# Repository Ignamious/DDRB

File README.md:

# DDRB 
This is a Digital Decade Resistor Box. This is the same as a Decade Resistor box, but uses an Arduino with LCD and Keypad to set the value. This will also allow the user to check the box and insure it's still within spec.

List of Features
  - LCD Readout of Resistance
  - Keypad to set resistance
  - Sub Ohm of .01 - .99 
  - Ohm 2^30 of Resistance ≈ 1,073,741,824 Ohms
  - Modular Cards, Easily replacable for Increased precistion (with Increase of Cst to the board)
  - 2 Expanstion Slots, Each with three Pins to the MCU (Future Expanstion) Signal Does Pass through these.
    - Possible uses
      - reading resistance from start to finish (will require slight rework of Buss Board)
      - Altering Resistance to give "True" value
      - Pulsed Output such as Sig Gen using Resistance values.
  - uses Binary Resistance values to get final resuslts:
    - 1 ohm + 2 ohm + 8 ohm = 11 ohms of resistance ECT. 
      - Should reduce cost

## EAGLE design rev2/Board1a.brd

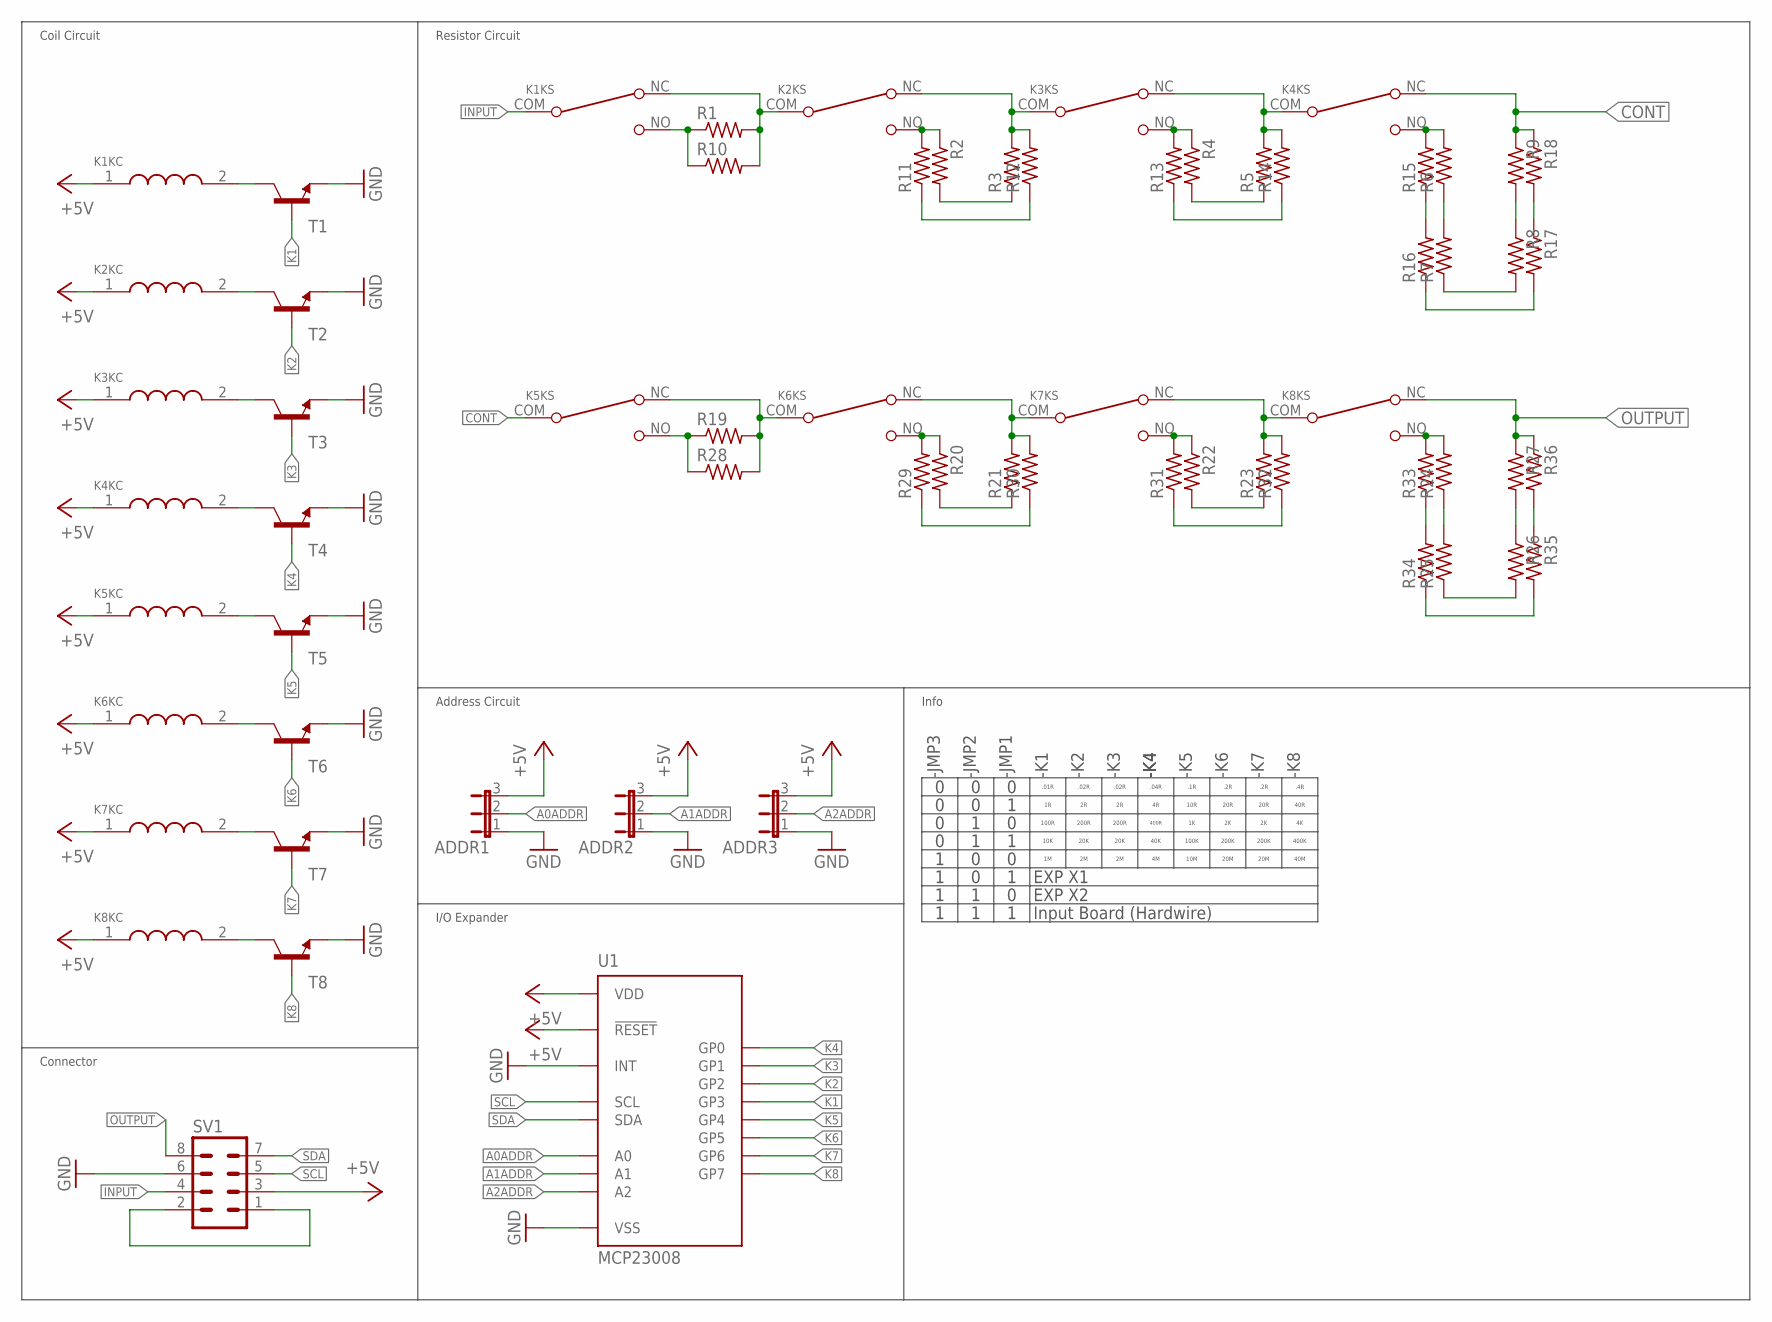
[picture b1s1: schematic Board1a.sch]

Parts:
ADDR1, ADDR2, ADDR3: JP2E; JP2
K1, K5: G5LE-1-VD DC12; G5LE
K2, K3, K4, K6, K7, K8: G5LE
R1, R2, R3, R4, R5, R6, R7, R8, R9, R19, R20, R21, R22, R23, R24, R25, R26, R27: R-US_0613/5V; P0613V
R10, R11, R12, R13, R14, R15, R16, R17, R18, R28, R29, R30, R31, R32, R33, R34, R35, R36: R-US_M1206; M1206
SV1: MA04-2
T1, T2, T3, T4, T5, T6, T7, T8: MMUN2211LT1-NPN-SC59-BEC; SC59-BEC
U1: MCP23008; SOIC

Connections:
+5V: ADDR1.3, ADDR2.3, ADDR3.3, K1.1 (COILA), K2.1 (COILA), K3.1 (COILA), K4.1 (COILA), K5.1 (COILA), K6.1 (COILA), K7.1 (COILA), K8.1 (COILA), SV1.3, U1.P$6 (!RESET), U1.P$18 (VDD)
A0ADDR: ADDR1.2, U1.P$5 (A0)
A1ADDR: ADDR2.2, U1.P$4 (A1)
A2ADDR: ADDR3.2, U1.P$3 (A2)
CONT: K4.NC, K5.COM, R9.1, R18.1
GND: ADDR1.1, ADDR2.1, ADDR3.1, SV1.6, T1.E, T2.E, T3.E, T4.E, T5.E, T6.E, T7.E, T8.E, U1.P$8 (INT), U1.P$9 (VSS)
INPUT: K1.COM, SV1.4
K1: T1.B, U1.P$13 (GP3)
K2: T2.B, U1.P$12 (GP2)
K3: T3.B, U1.P$11 (GP1)
K4: T4.B, U1.P$10 (GP0)
K5: T5.B, U1.P$14 (GP4)
K6: T6.B, U1.P$15 (GP5)
K7: T7.B, U1.P$16 (GP6)
K8: T8.B, U1.P$17 (GP7)
unnamed: K1.NO, R1.1, R10.1
unnamed: K1.NC, K2.COM, R1.2, R10.2
unnamed: R2.2, R3.1
unnamed: K2.NC, K3.COM, R3.2, R12.2
unnamed: SV1.1, SV1.2
unnamed: K2.NO, R2.1, R11.2
unnamed: K3.NC, K4.COM, R5.2, R14.2
unnamed: K3.NO, R4.1, R13.2
unnamed: K4.NO, R6.2, R15.2
unnamed: R4.2, R5.1
unnamed: K3.2 (COILB), T3.C
unnamed: R6.1, R7.2
unnamed: K1.2 (COILB), T1.C
unnamed: R7.1, R8.2
unnamed: K2.2 (COILB), T2.C
unnamed: R8.1, R9.2
unnamed: K4.2 (COILB), T4.C
unnamed: R15.1, R16.2
unnamed: R16.1, R17.2
unnamed: R17.1, R18.2
unnamed: R11.1, R12.1
unnamed: R13.1, R14.1
unnamed: K5.NC, K6.COM, R19.2, R28.2
unnamed: K6.NC, K7.COM, R21.2, R30.2
unnamed: K7.NC, K8.COM, R23.2, R32.2
unnamed: K5.NO, R19.1, R28.1
unnamed: R20.2, R21.1
unnamed: K6.NO, R20.1, R29.2
unnamed: K7.NO, R22.1, R31.2
unnamed: R22.2, R23.1
unnamed: K8.NO, R24.2, R33.2
unnamed: R24.1, R25.2
unnamed: R25.1, R26.2
unnamed: R26.1, R27.2
unnamed: R33.1, R34.2
unnamed: R34.1, R35.2
unnamed: R35.1, R36.2
unnamed: R29.1, R30.1
unnamed: R31.1, R32.1
unnamed: K7.2 (COILB), T7.C
unnamed: K5.2 (COILB), T5.C
unnamed: K6.2 (COILB), T6.C
unnamed: K8.2 (COILB), T8.C
OUTPUT: K8.NC, R27.1, R36.1, SV1.8
SCL: SV1.5, U1.P$1 (SCL)
SDA: SV1.7, U1.P$2 (SDA)

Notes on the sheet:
-JMP3
-JMP2
-JMP1
-K1
-K2
-K3
-K4
.01R
.1R
.02R
.04R
.2R
.4R
10R
100R
20R
200R
40R
400R
10K
100K
20K
200K
40K
400K
-K5
-K6
-K7
-K8
Coil Circuit
Connector
Resistor Circuit
Address Circuit
I/O Expander
Info
10M
20M
40M
EXP X1
EXP X2

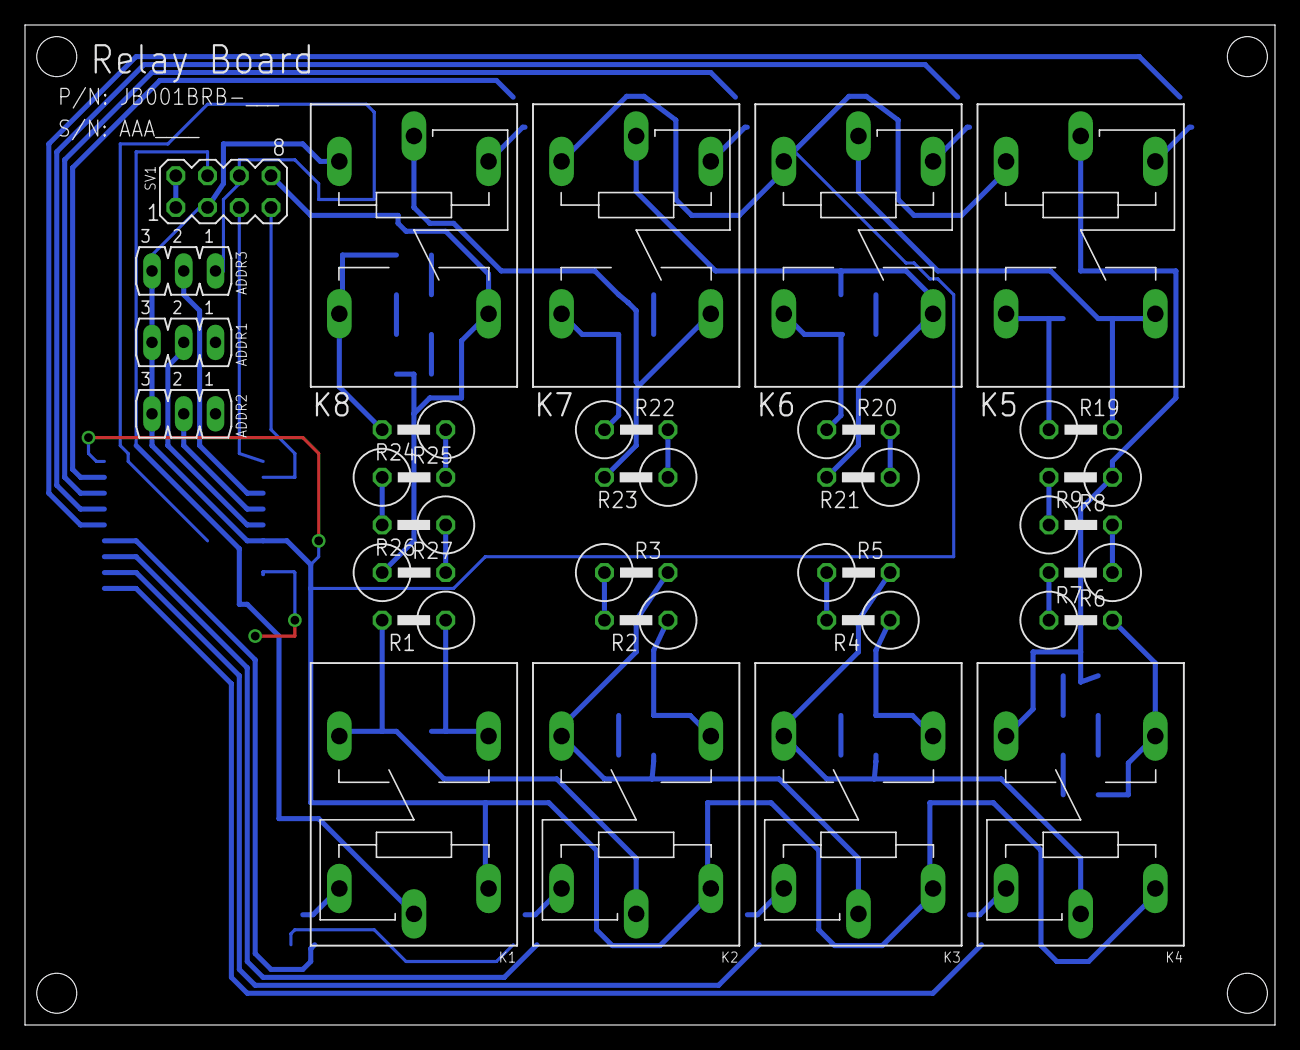
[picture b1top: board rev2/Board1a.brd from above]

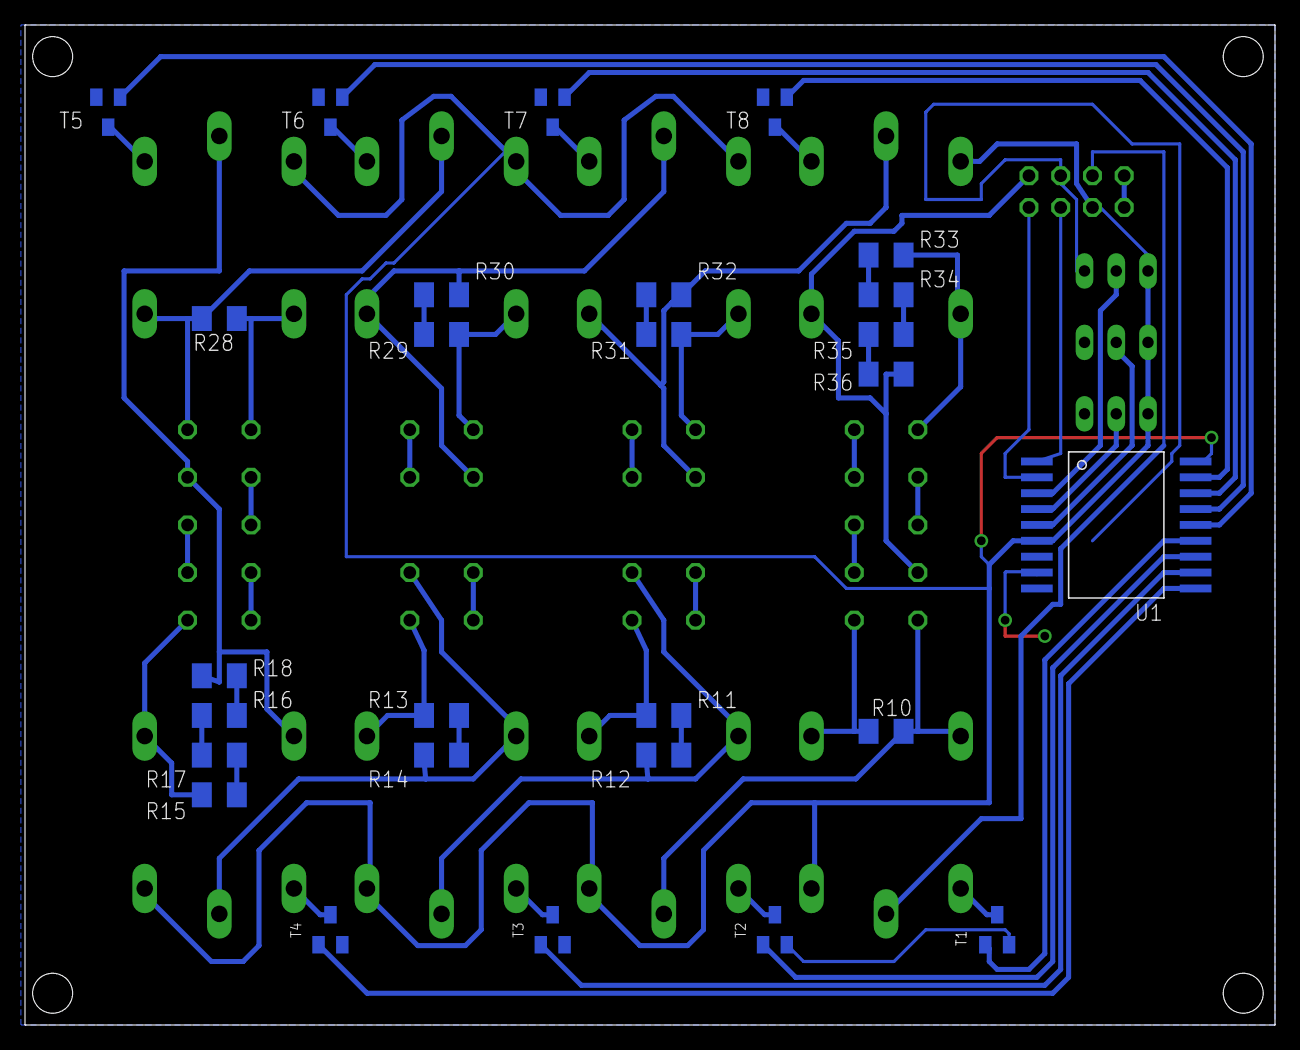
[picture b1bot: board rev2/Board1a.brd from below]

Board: 2 copper layers, 100.0 x 80.0 mm, 57 parts (27 on the bottom side), 61 nets.

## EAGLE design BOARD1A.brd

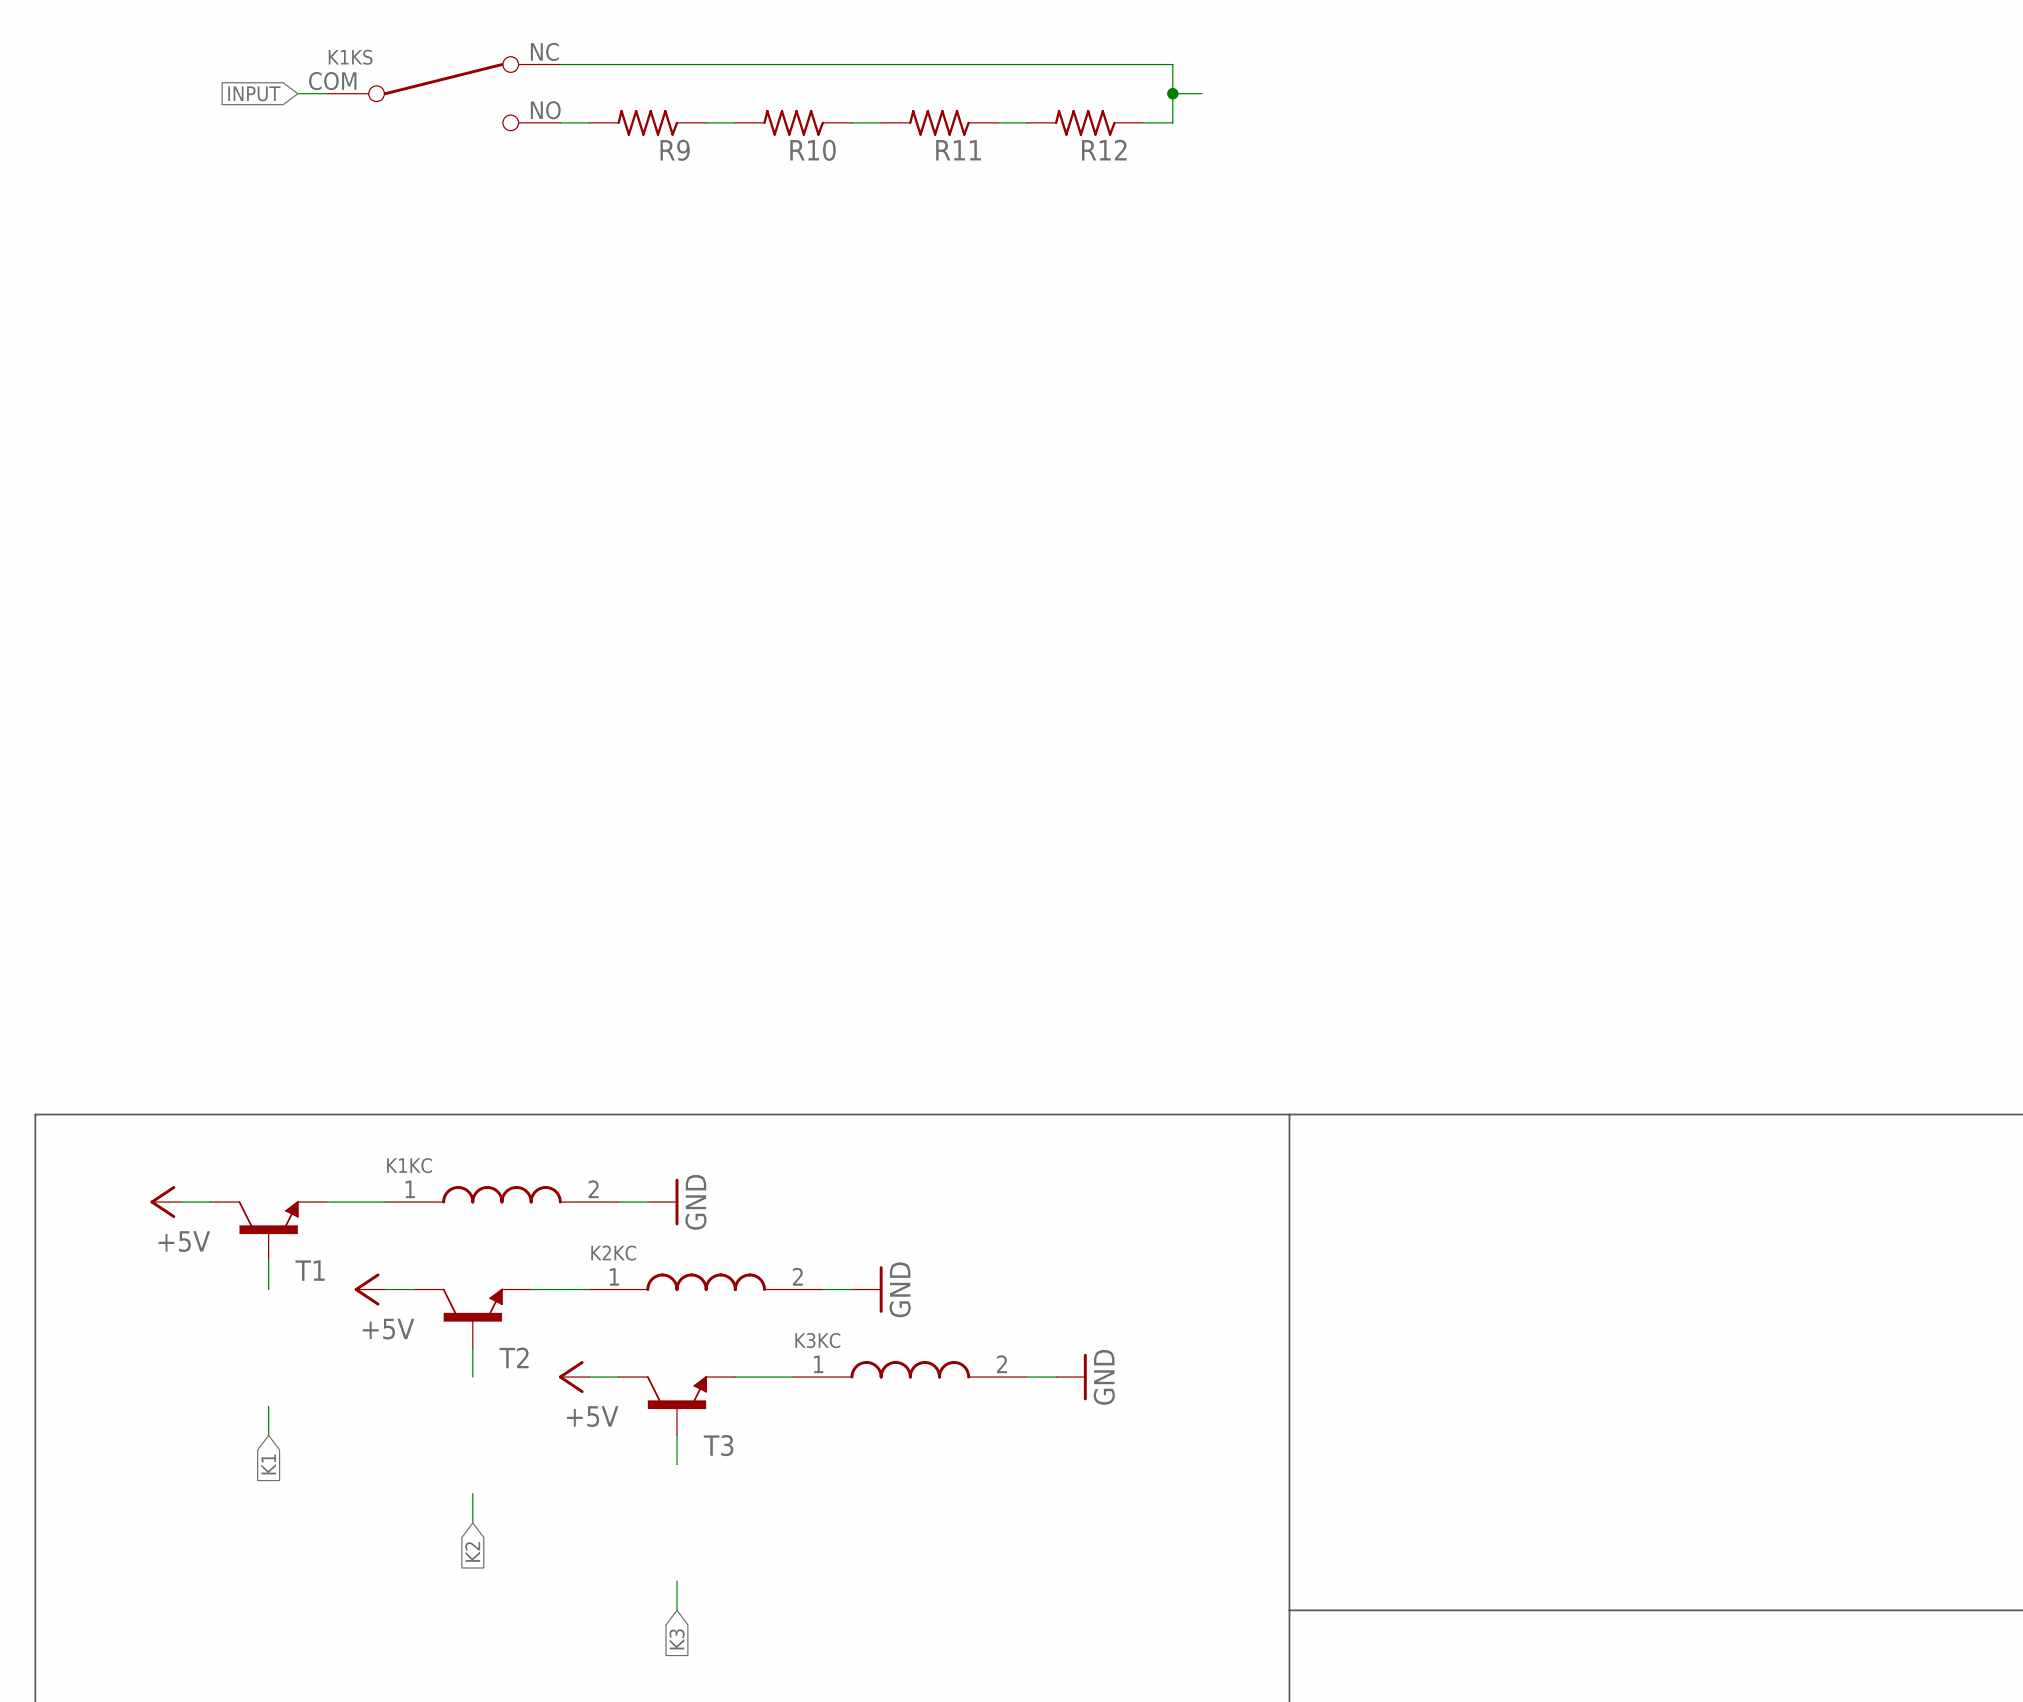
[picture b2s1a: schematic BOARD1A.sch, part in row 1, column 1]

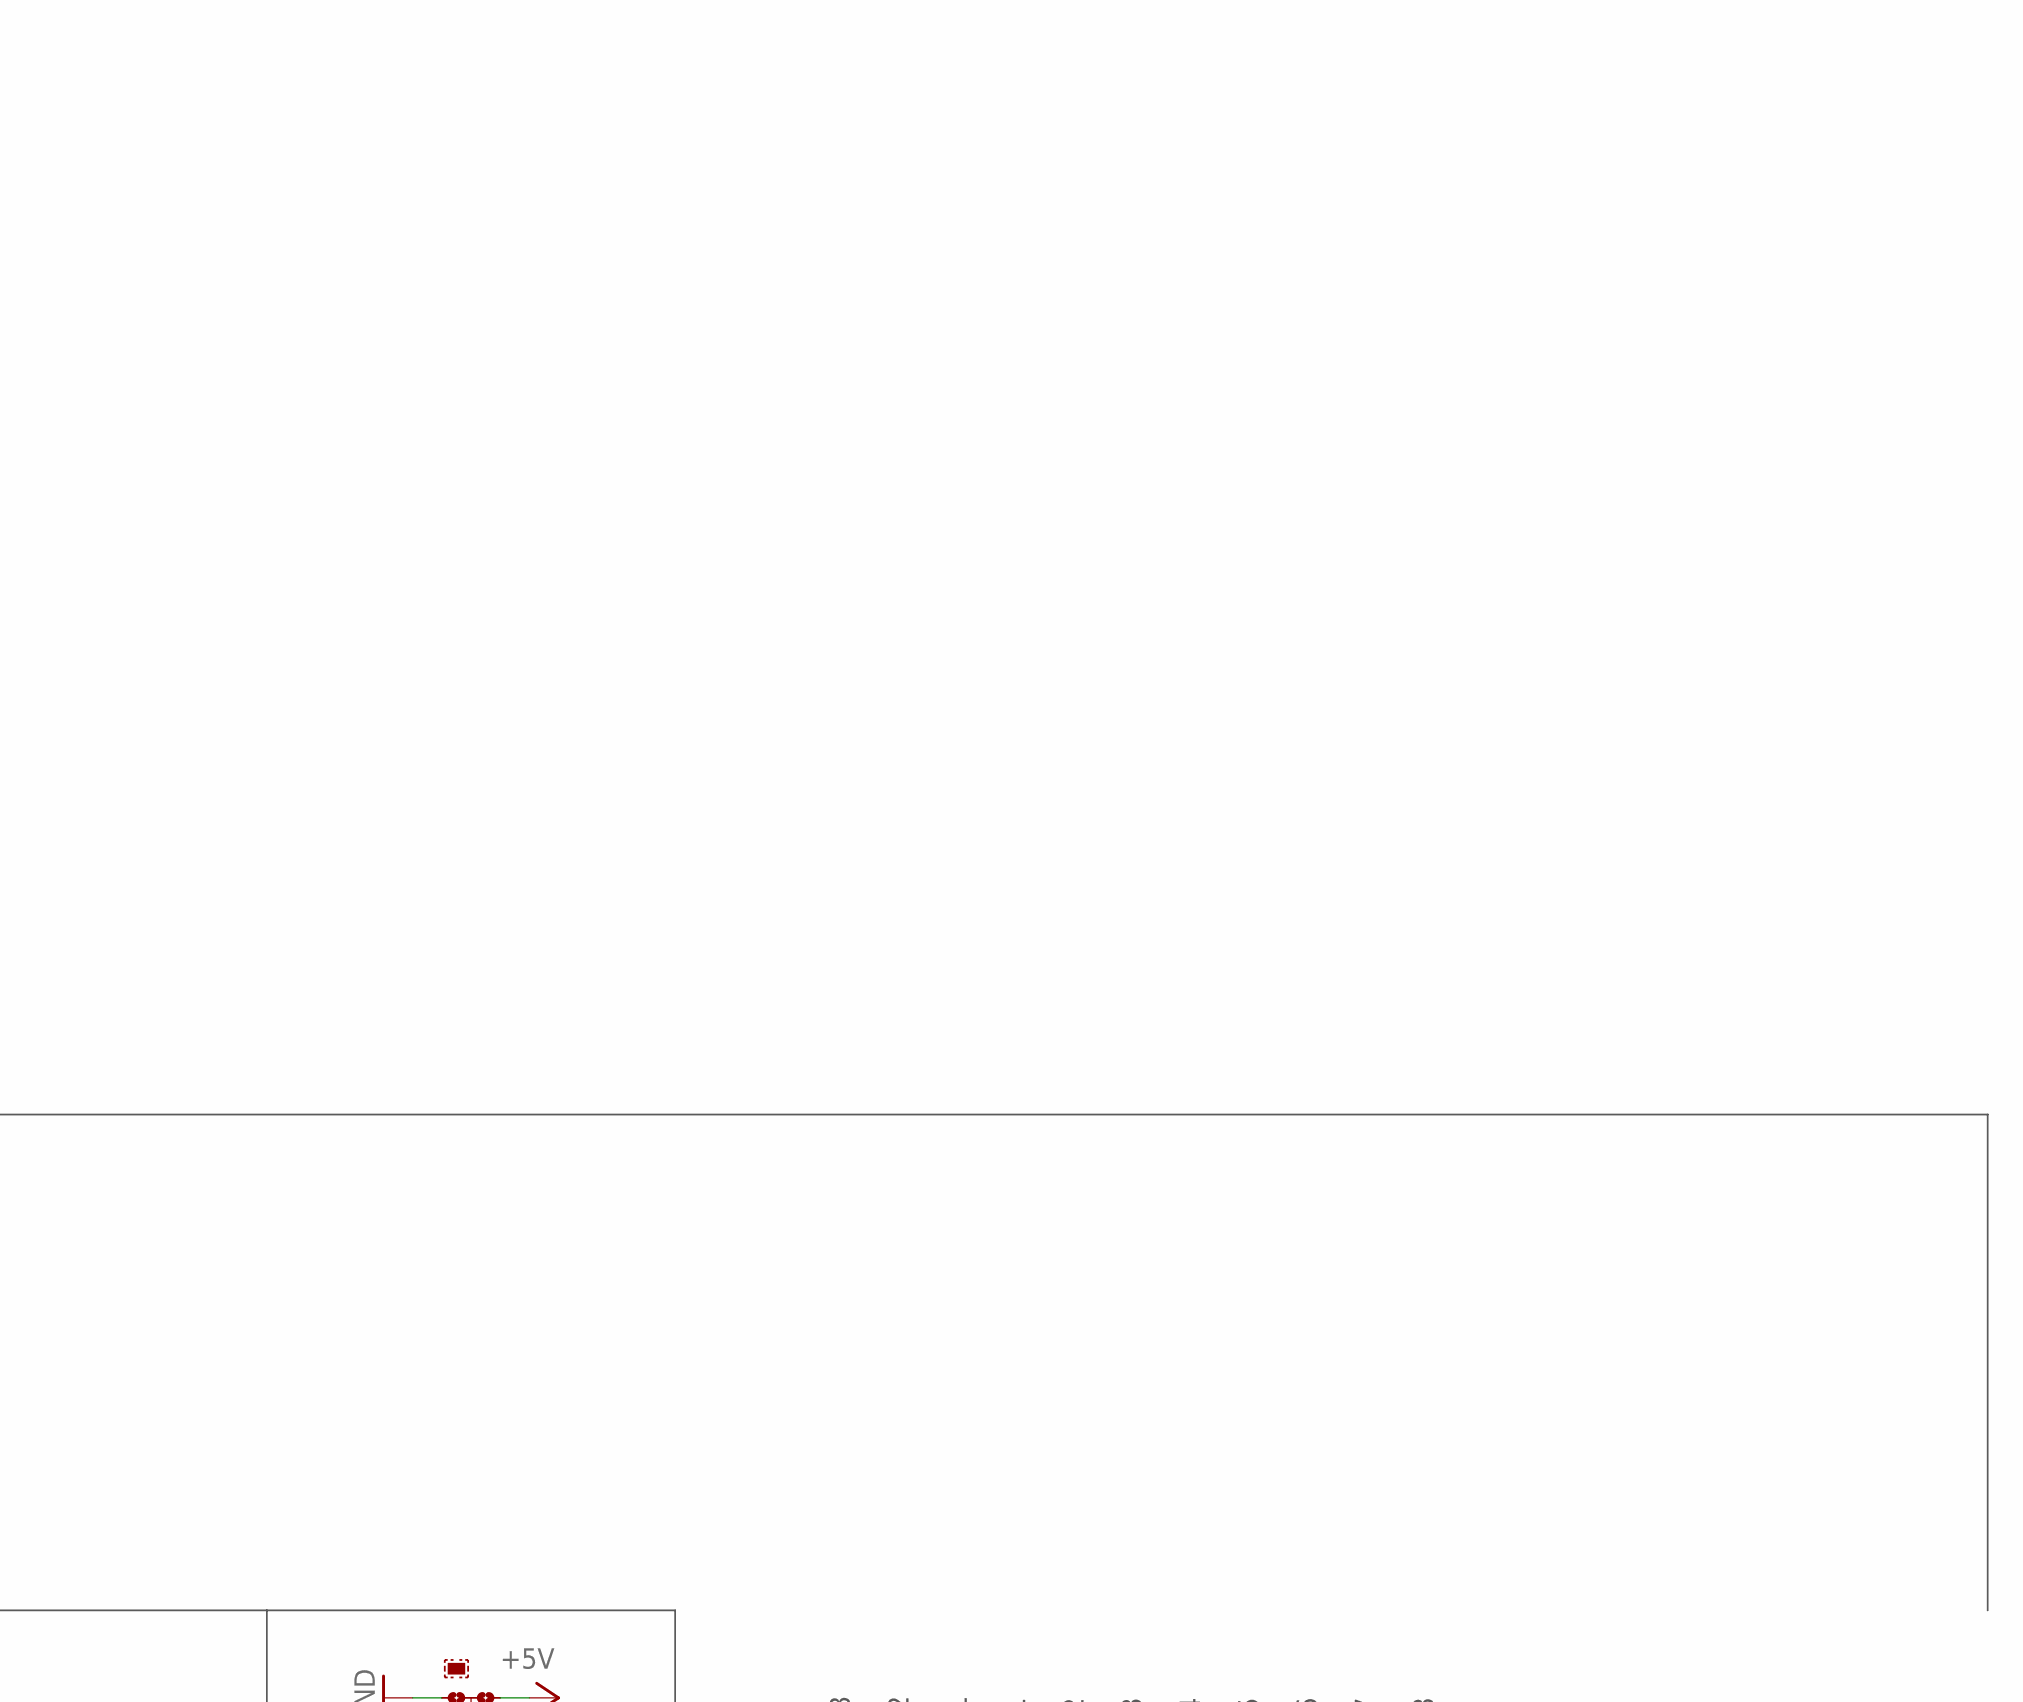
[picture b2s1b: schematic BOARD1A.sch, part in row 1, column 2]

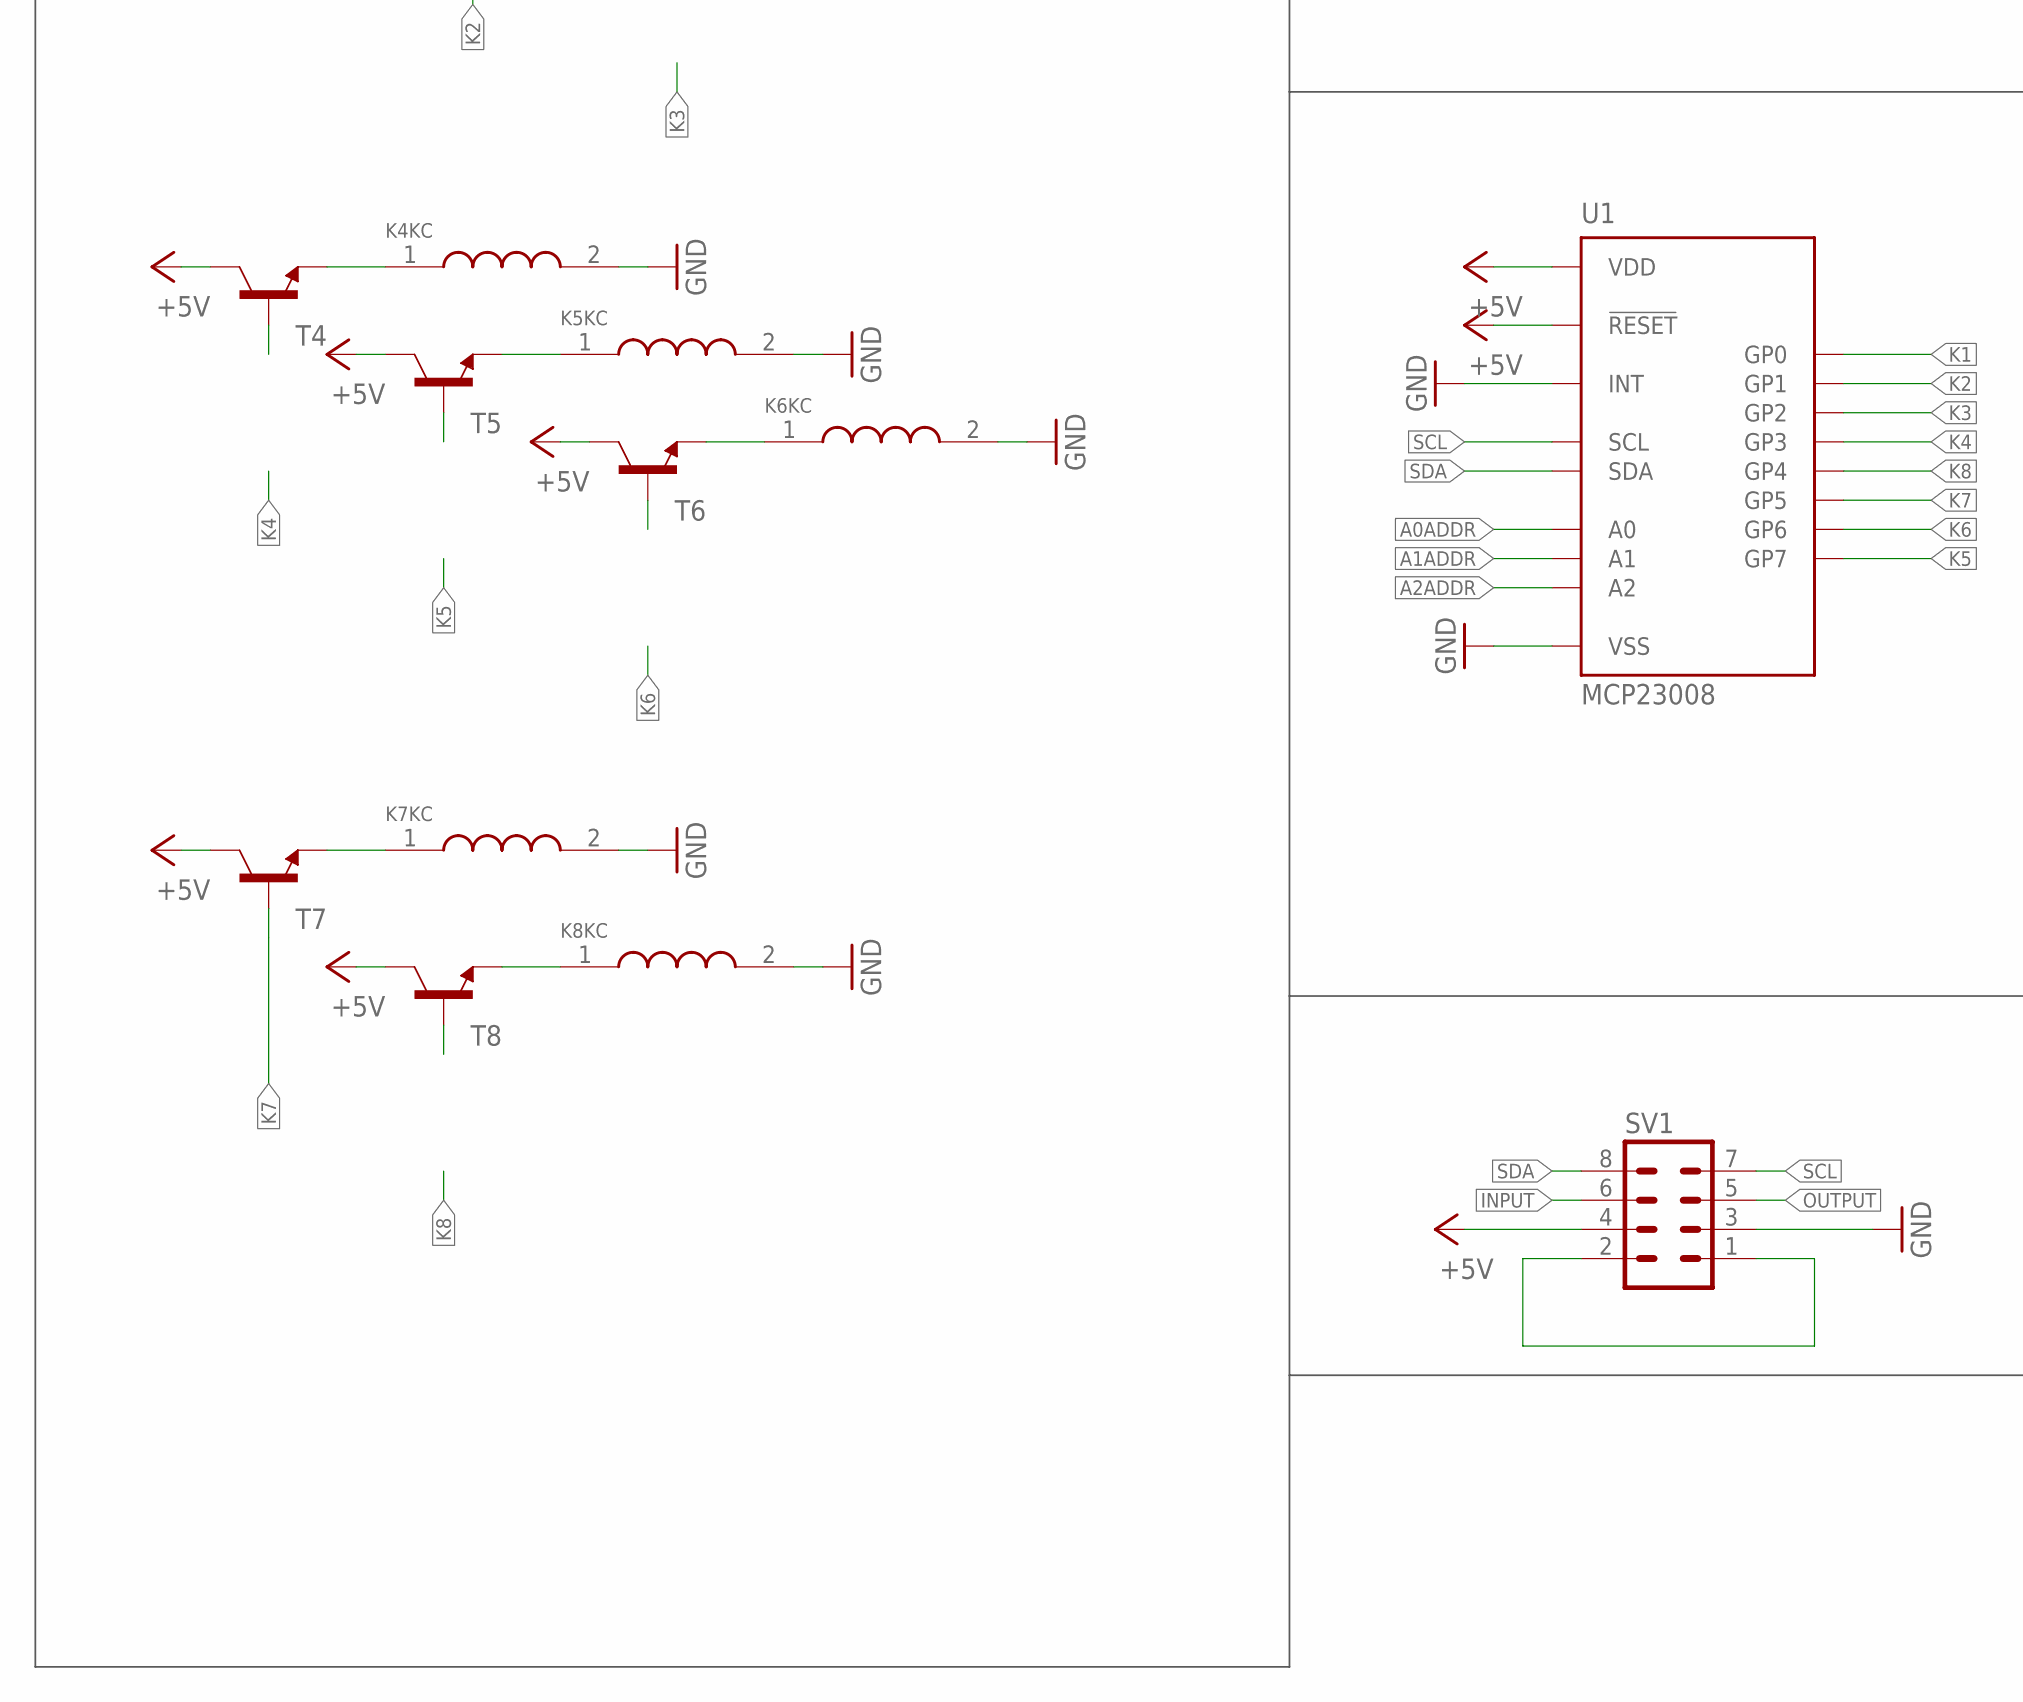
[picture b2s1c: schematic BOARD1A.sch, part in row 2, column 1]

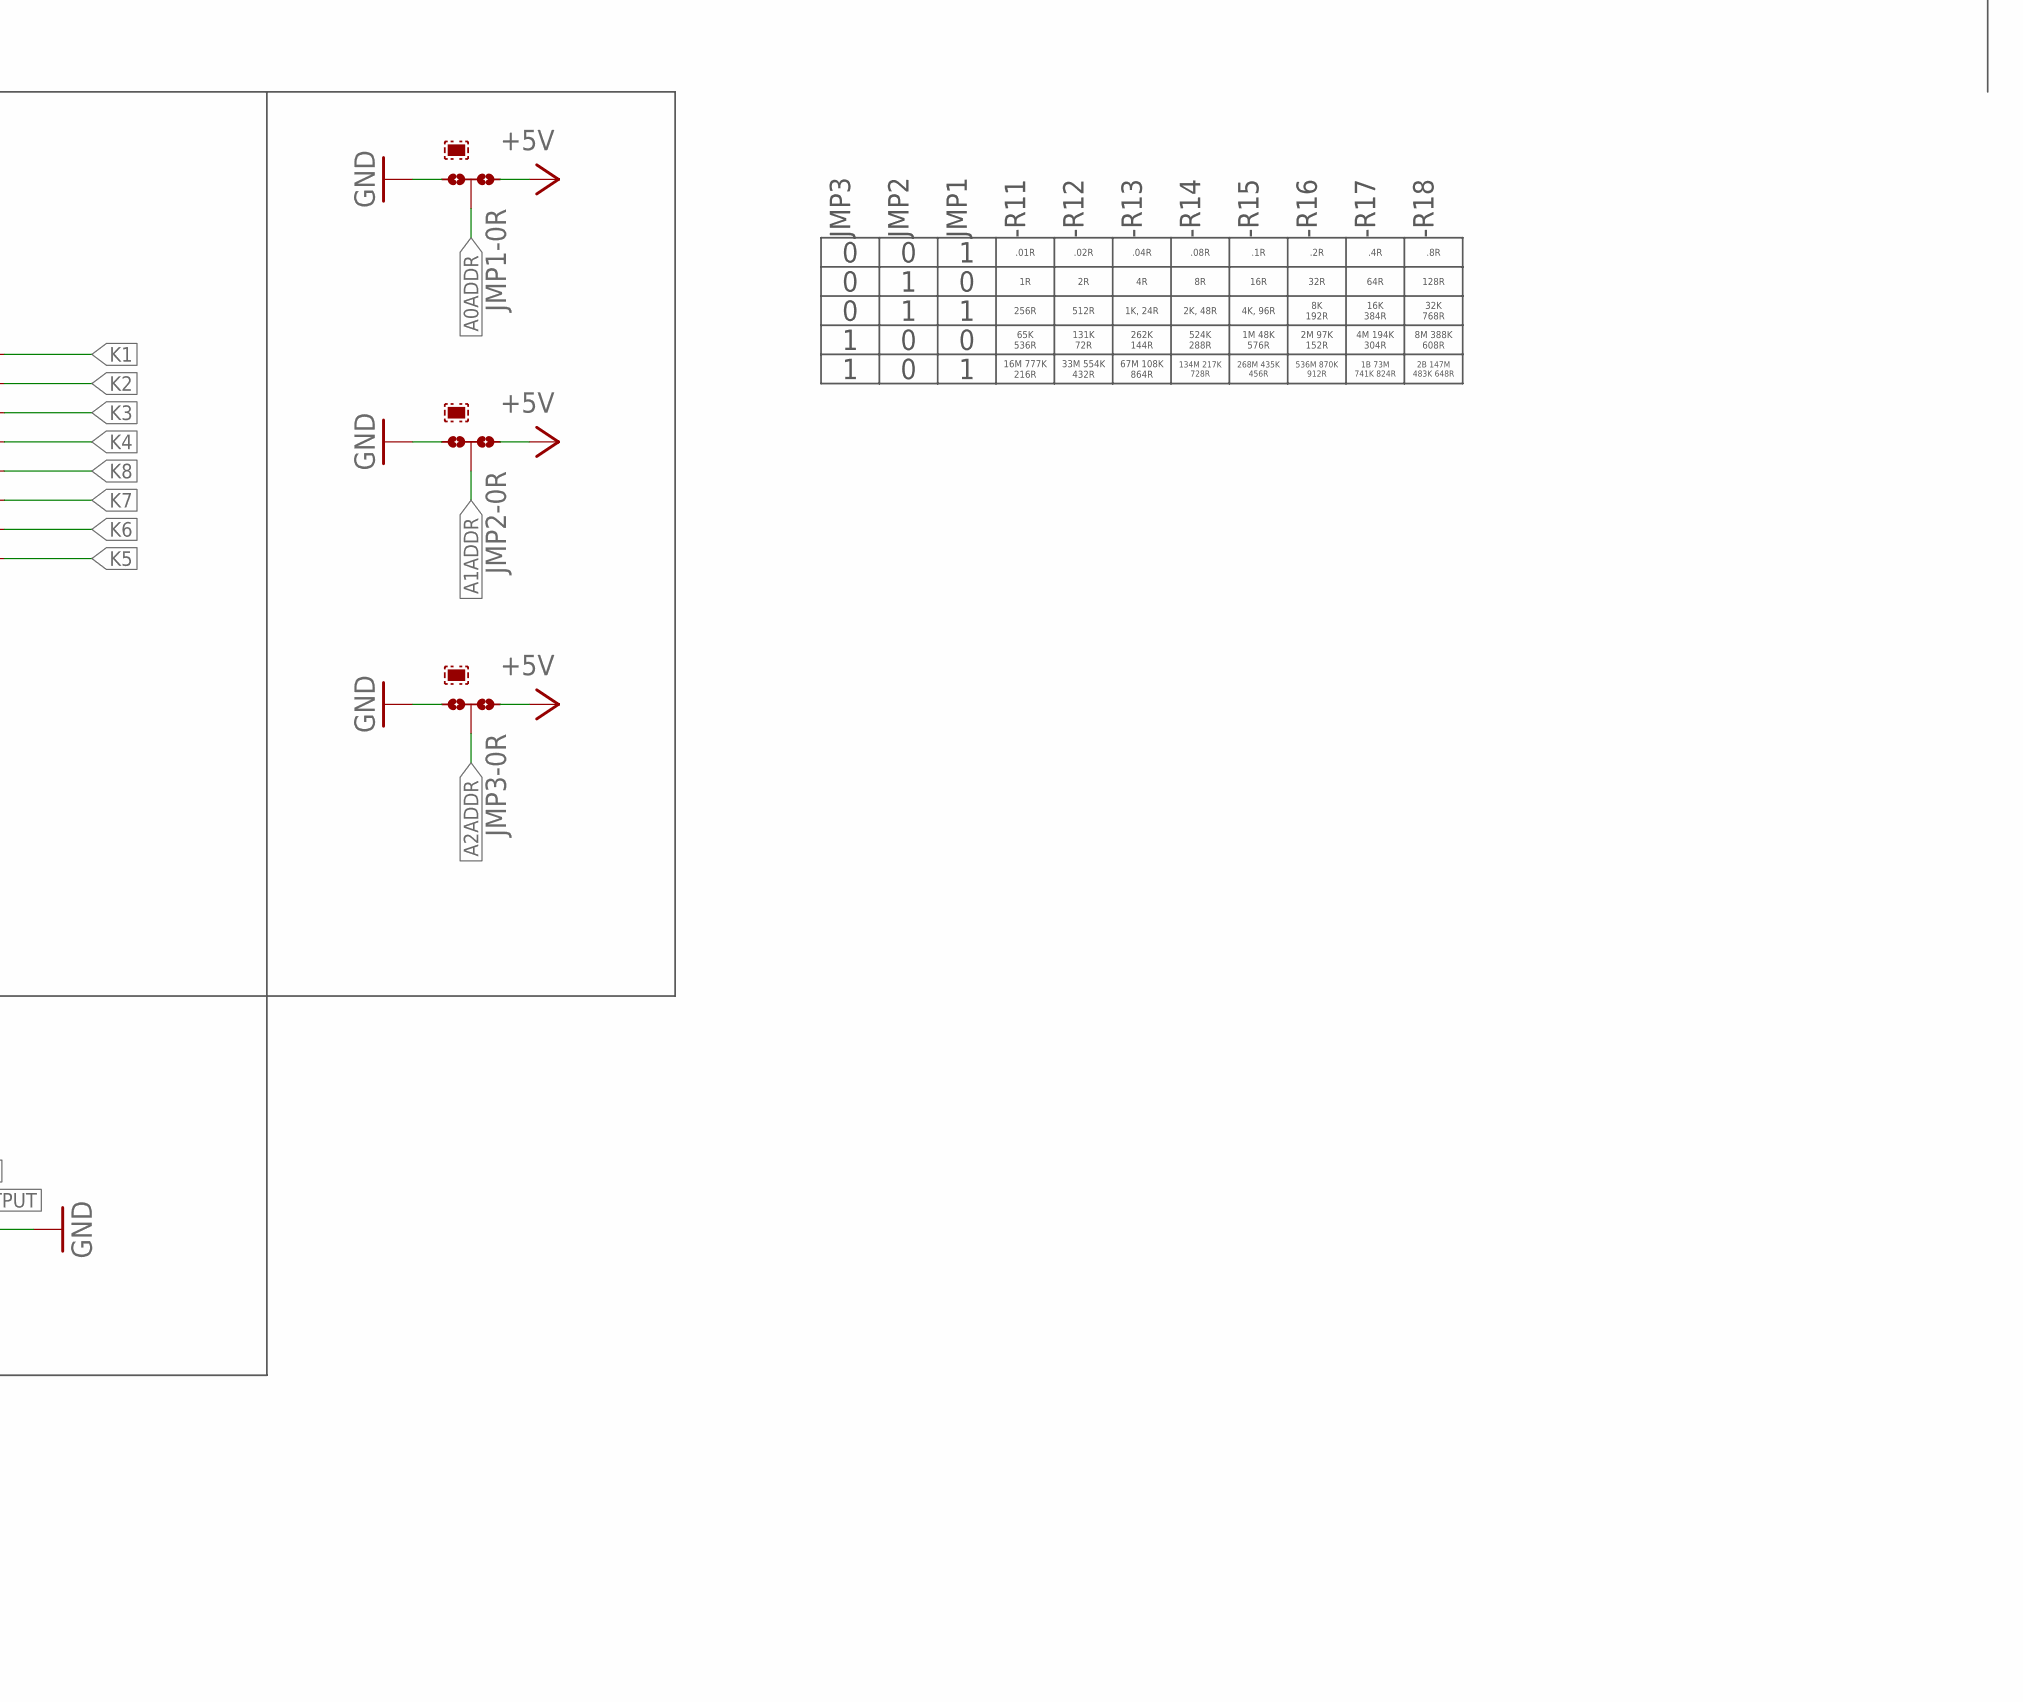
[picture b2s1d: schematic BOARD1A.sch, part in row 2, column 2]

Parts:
JMP1, JMP2, JMP3: 0R-JUMPA; A0R-JMP
K1: G5LE-1-VD DC12; G5LE
K2, K3, K4, K5, K6, K7, K8: G5LE
R9, R10, R11, R12: R-US_0207/12; 0207/12
SV1: MA04-2
T1, T2, T3, T4, T5, T6, T7, T8: MMUN2211LT1-NPN-SC59-BEC; SC59-BEC
U1: MCP23008; SOIC

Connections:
+5V: JMP1.1, JMP2.1, JMP3.1, SV1.4, T1.C, T2.C, T3.C, T4.C, T5.C, T6.C, T7.C, T8.C, U1.P$6 (!RESET), U1.P$18 (VDD)
A0ADDR: JMP1.2, U1.P$5 (A0)
A1ADDR: JMP2.2, U1.P$4 (A1)
A2ADDR: JMP3.2, U1.P$3 (A2)
GND: JMP1.3, JMP2.3, JMP3.3, K1.2 (COILB), K2.2 (COILB), K3.2 (COILB), K4.2 (COILB), K5.2 (COILB), K6.2 (COILB), K7.2 (COILB), K8.2 (COILB), SV1.3, U1.P$8 (INT), U1.P$9 (VSS)
INPUT: K1.COM, SV1.6
K1: U1.P$10 (GP0)
K2: U1.P$11 (GP1)
K3: U1.P$12 (GP2)
K4: U1.P$13 (GP3)
K5: U1.P$17 (GP7)
K6: U1.P$16 (GP6)
K7: U1.P$15 (GP5)
K8: U1.P$14 (GP4)
unnamed: K1.NO, R9.2
unnamed: R9.1, R10.2
unnamed: R10.1, R11.2
unnamed: R11.1, R12.2
unnamed: SV1.1, SV1.2
unnamed: K1.NC, R12.1
unnamed: K1.1 (COILA), T1.E
unnamed: K2.1 (COILA), T2.E
unnamed: K3.1 (COILA), T3.E
unnamed: K4.1 (COILA), T4.E
unnamed: K5.1 (COILA), T5.E
unnamed: K6.1 (COILA), T6.E
unnamed: K7.1 (COILA), T7.E
unnamed: K8.1 (COILA), T8.E
OUTPUT: SV1.5
SCL: SV1.7, U1.P$1 (SCL)
SDA: SV1.8, U1.P$2 (SDA)

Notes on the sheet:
JMP3
JMP2
JMP1
-R11
-R12
-R13
-R14
-R15
-R16
-R17
-R18
.01R
.02R
.04R
.08R
.1R
.2R
.4R
.8R
16R
32R
64R
128R
256R
65K 536R
16M 777K 216R
512R
131K 72R
33M 554K 432R
1K, 24R
262K 144R
67M 108K 864R
2K, 48R
524K 288R
134M 217K 728R
4K, 96R
1M 48K 576R
268M 435K 456R
8K 192R
2M 97K 152R

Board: 2 copper layers, 25 parts (0 on the bottom side), 22 nets, no tracks yet.

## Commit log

2015-09-11 First Upload
    The First upload to my DDRB
2015-09-11 Added Silk Screen
    Added Silk Screen
2015-09-12 Added Silk Screens, Changed Layout some.
2015-09-13 Added Code
    This code is POC only mostly LCD Info was added not much to see yet.
2015-09-14 Changed Parts
    Changed relay from 5VDC Coil to 12 VDC so it’s only 40mA. Changed to
    SOT-23 SBT Transistor (100mA capability). removed bias resistors.
2015-09-18 Updated Design Rev2 Current
    Current Design is now Rev 2. At this time looks like i can get all the
    parts needed to do this one.
2015-09-21 more work

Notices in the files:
parts and their libraries:
SparkFun: Licensing: CC v3.0 Share-Alike You are welcome to use this library for commercial purposes.
